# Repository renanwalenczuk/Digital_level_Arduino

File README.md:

# Digital_level_Arduino
Projeto criado no curso Criação de protótipos com Arduino.

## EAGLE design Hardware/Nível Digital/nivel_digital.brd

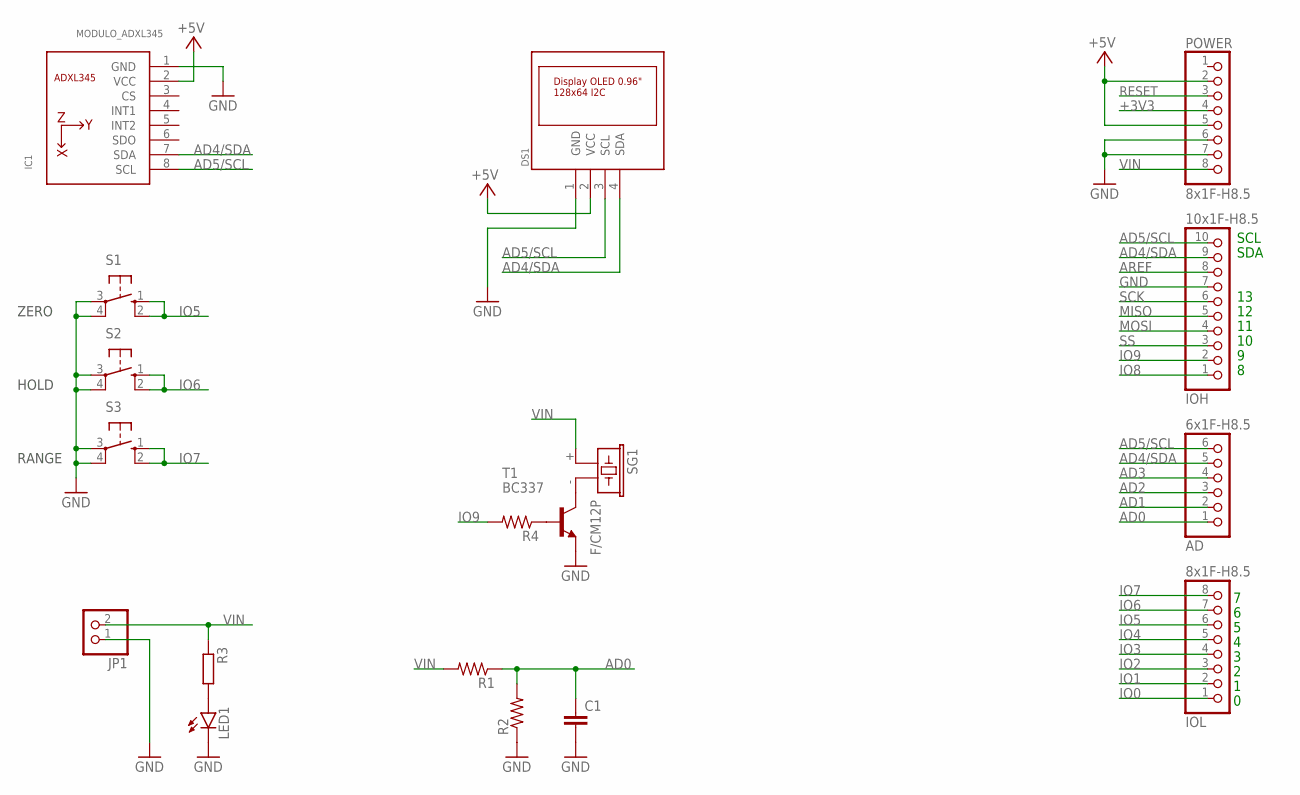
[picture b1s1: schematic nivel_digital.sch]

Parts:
AD: 6x1F-H8.5; 1X06
C1: C-EU050-025X075; C050-025X075
DS1: OLED_0.96_I2C
IC1: MODULO_ADXL345
IOH: 10x1F-H8.5; 1X10
IOL: 8x1F-H8.5; 1X08
JP1: PINHD-1X2/90; 1X02/90
LED1: LED5MM
POWER: 8x1F-H8.5; 1X08
R1, R2, R4: R-US_0204/7; 0204/7
R3: R-EU_0207/10; 0207/10
S1, S2, S3: 10-XXPUSH-BUTTON-5MM; B3F-10XX
SG1: F/CM12P
T1: BC337; TO92

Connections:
+3V3: POWER.4
+5V: DS1.2 (VCC), IC1.2 (VCC), POWER.2, POWER.5
AD0: AD.1, C1.1, R1.1, R2.2
AD1: AD.2
AD2: AD.3
AD3: AD.4
AD4/SDA: AD.5, DS1.4 (SDA), IC1.7 (SDA), IOH.9
AD5/SCL: AD.6, DS1.3 (SCL), IC1.8 (SCL), IOH.10
AREF: IOH.8
GND: C1.2, DS1.1 (GND), IC1.1 (GND), IOH.7, JP1.1, LED1.K (C), POWER.6, POWER.7, R2.1, S1.3, S1.4 (P1), S2.3, S2.4 (P1), S3.3, S3.4 (P1), T1.1 (E)
IO0: IOL.1
IO1: IOL.2
IO2: IOL.3
IO3: IOL.4
IO4: IOL.5
IO5: IOL.6, S1.1 (S), S1.2 (S1)
IO6: IOL.7, S2.1 (S), S2.2 (S1)
IO7: IOL.8, S3.1 (S), S3.2 (S1)
IO8: IOH.1
IO9: IOH.2, R4.2
MISO: IOH.5
MOSI: IOH.4
unnamed: LED1.A, R3.2
unnamed: SG1.- (2), T1.3 (C)
unnamed: R4.1, T1.2 (B)
RESET: POWER.3
SCK: IOH.6
SS: IOH.3
VIN: JP1.2, POWER.8, R1.2, R3.1, SG1.+ (1)

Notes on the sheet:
SDA
SCL
ZERO
HOLD
RANGE

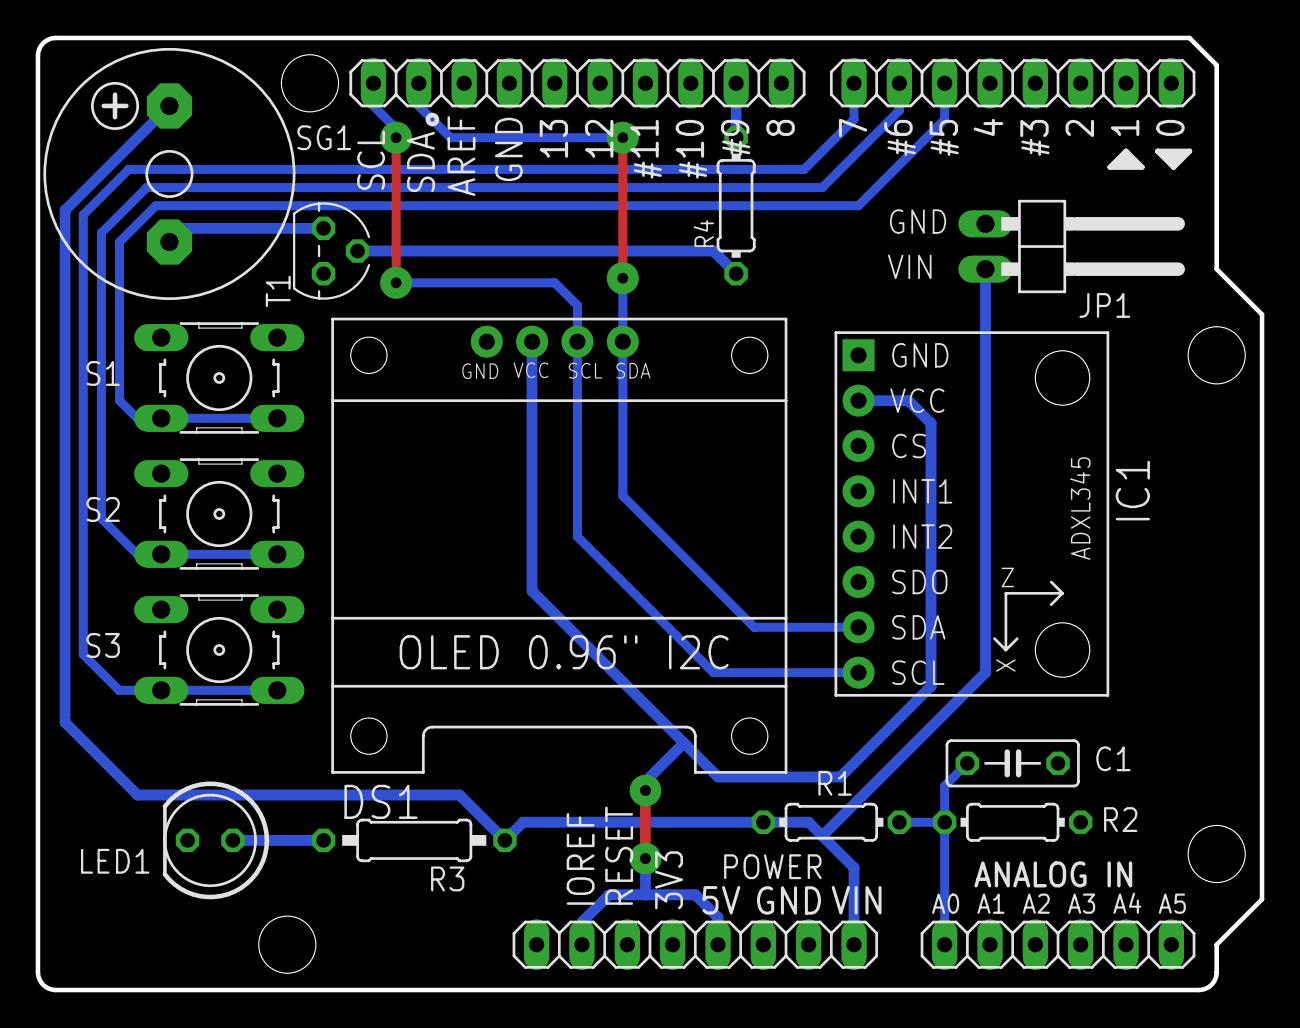
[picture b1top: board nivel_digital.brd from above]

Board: 2 copper layers, 68.6 x 53.3 mm, 18 parts (0 on the bottom side), 13 nets.

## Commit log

2022-05-18 Primeiro commit!
2022-05-18 icone do angulo
2022-05-22 Todos os bitmaps
2022-05-23 zero relativo + hold + orientação automática
2022-05-24 Formatação do ângulo
2022-05-25 Botão range adicionado
2022-06-04 Botao Range + pinagem dos botões
2022-06-22 Display e acelerômetro novos
2022-06-23 versao 1.0
2022-06-23 Comentários
